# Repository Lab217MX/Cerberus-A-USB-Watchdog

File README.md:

# Cerberus

<p align="center">
  <strong>Developed by Lab217</strong><br>
  No USB gets in without permission. NONE
</p>

<p align="center">
  <sub>Proudly sponsored by</sub><br>
  
</p>

**🌐 [English](README.md) · [Español](README.es.md) · [Português](README.pt.md)**

---

## What is Cerberus?

**Cerberus is a pocket-sized device where you plug in any suspicious USB to see, in real time, what it tries to do to a computer — before you risk your own.**

Instead of blindly trusting a flash drive you found or were handed, you plug it into Cerberus first: the device pretends to be a normal PC, watches how the USB behaves, and instantly warns you if it tries to type on its own (BadUSB / Rubber Ducky), read or write files without permission, or fry the port with a voltage spike (USB Killer). Everything is shown on an OLED screen, a color LED, and over the serial port.

### Key features

- **Detects BadUSB / Rubber Ducky** — spots automated typing that's impossible for a human.
- **Detects USB Killer** — alerts on high-voltage spikes (and blocks them with the optional isolator).
- **Watches reads and writes** — warns if the USB tries to read `AUTORUN`/`README` or write/delete files on its own.
- **Suspicious-device database** — recognizes known attack hardware by its VID/PID.
- **On-device file analyzer** — recursively lists every file on the drive and identifies each one by its **magic bytes** (PNG, PDF, ELF, PE/EXE, ZIP, …), flagging files whose real type doesn't match their extension (e.g. an `.jpg` that is actually an executable). Reads file contents only, never executes.
- **Archive & polyglot inspection** — looks *inside* ZIP archives (via the central directory) for embedded executables/scripts and sweeps files for signatures hidden *after* a valid header (appended payloads / polyglots). Signature-only — nothing is decompressed, so it is immune to zip bombs.
- **Redesigned OLED GUI** — dedicated screens for the home/self-test, mass-storage detection, options menu, USB descriptors, file analyzer, hex viewer, and wipe confirmation, with on-screen `Ok`/`Bak` hints.
- **Full visibility** — OLED screen, NeoPixel LED, and serial console showing everything that happens.
- **Forensics & red team** — captures keystrokes, exports to DuckyScript, and stores info on the last device.
- **Neutralize suspicious drives** — manually wipe the MBR/GPT tables of the mounted USB (from the on-device **Wipe** menu or the `WIPE` serial command); never triggered automatically.

> Built for cybersecurity professionals (SOC, blue team, and red team) as a USB test bench, BadUSB payload debugger, and basic forensic triage tool. Built on top of [USBvalve](https://github.com/cecio/USBvalve).

---

## Installation

### Prerequisites

- Install the Arduino IDE
- `Adafruit TinyUSB Library` version `>=3.6.0`
- `Pico-PIO-USB` version `>=0.7.2`
- Boards `Raspberry Pi RP2040 (4.5.4)` with CPU Speed at `133MHz` and Tools => USB Stack set to `Adafruit TinyUSB`
- `Adafruit_SSD1306` OLED library version `>=2.5.14`
- Raspberry Pi Pico 1 or 2 (or another RP2040-based dev board)
- 128x64 or 128x32 I2C OLED display (SSD1306)

### Steps

---

#### Using the precompiled version

In GitHub, go to Releases and find the most recent `.uf2` file, then download it.

To flash the image:

- Connect the Raspberry Pi Pico with a USB cable while holding the _BOOTSEL/BOOT_ button.
- Release the button.
- A new device named `RPI-RP2` will appear on your system (on Linux you'll probably have to mount it manually).
- Copy the `.uf2` file into the folder, depending on your OLED display.
- Wait a few seconds until the device disappears.

#### Compile your own version

Get the repo locally:

```bash
git clone https://github.com/Glitchboi-sudo/Cerberus-A-USB-Watchdog.git
```

With the Arduino IDE:

- Open `Software/Cerberus/Cerberus.ino`.
- Connect the Raspberry Pi Pico with a USB cable.
- Select the Pico in Arduino.
- Tools -> USB Stack -> Adafruit TinyUSB
- Click `Upload`.

---

## Usage

The idea is simple: **Cerberus sits between your computer and the USB you want to inspect**, acting as a decoy so the suspicious device reveals its real behavior.

### Step by step

1. **Power Cerberus.** Connect it to your computer with a USB cable (the RP2040's native port). On boot, the OLED shows the home screen with "Self-Test:ok" and the LED turns **blue**: ready to go.
2. **Plug the suspicious USB** into Cerberus's host port (not into your computer).
3. **Watch the reaction in real time.** Cerberus pretends to be a PC and lets the device act. The screen, the LED, and the serial console tell you immediately what it's trying to do.
4. **Read the verdict** using the indicator table below: blue = normal, red/orange/magenta = suspicious.
5. **Inspect a storage device.** When a mass-storage drive is attached, the OLED shows a **Mass storage** detection screen; press **Ok** to open the options menu — **Info** (USB descriptors), **Files** (the magic-byte file analyzer), and **Wipe** (neutralize partition tables). In the file analyzer, pick any file to see its detected type, size, and a hex view, plus a warning if it hides an executable/appended payload.
6. **(Optional) Dig deeper over serial** for forensic analysis, keystroke capture, and the `SCAN` / `INSPECT` commands (see below).

### Screen and LED indicators

| Event                       | OLED message       | LED color |
| --------------------------- | ------------------ | --------- |
| Ready/Normal (home)         | "Self-Test:ok"     | Blue      |
| README read                 | "README (R)"       | Blue      |
| AUTORUN read                | "AUTORUN (R)"      | Blue      |
| Write detected              | "WRITING"          | Blue      |
| Delete detected             | "DELETING"         | Blue      |
| HID device connected        | "HID Device"       | Red       |
| HID sending data            | "HID Sending data" | Red       |
| Suspicious device           | "SUSP: [name]"     | Orange    |
| Automated typing (BadUSB)   | "AUTO [X] k/s"     | Magenta   |
| USB Killer detected         | "USB Killer"       | Red       |
| Mass storage detected       | "Mass storage"     | Green     |
| Wipe in progress            | "WIPING DISK"      | —         |
| Wipe complete               | "WIPE DONE"        | —         |
| Wipe error                  | "WIPE ERROR"       | —         |

### Physical buttons

The OLED is driven by four soft-keys. Every screen shows `Ok` / `Bak` hints in the bottom-right; `Up` / `Down` move the selection where a list is shown.

- **Ok** (Accept): open the options menu when a device is attached (on the home screen), enter the highlighted item, toggle hex/ASCII in the hex viewer, and confirm a wipe. On the "No device" screen, any key returns home.
- **Up / Down**: move through menu items and file lists.
- **Bak**: go back one level / exit a menu (disabled on the mass-storage detection screen, which only opens the menu).
- **BOOTSEL**:
  - Short press: reboot the device
  - Press >2 s: show the HID event count

USB descriptor pages and the partition wipe now live inside the on-device **Info** and **Wipe** menu items (no more button-hold shortcuts).

### Serial port commands

Connect over serial (SerialTinyUSB) and type these commands:

| Command    | Description                                |
| ---------- | ------------------------------------------ |
| `HELP`     | Show the list of commands                  |
| `STATUS`   | Current device status                      |
| `LAST`     | Forensic info on the last connected device |
| `RESET`    | Reset counters                             |
| `REBOOT`   | Reboot the device                          |
| `VERBOSE`  | Toggle verbose mode                        |
| `HEXDUMP`  | Toggle hex dump                            |
| `HIDDEBUG` | Toggle HID debug (raw bytes)               |
| `CLEAR`    | Clear info on the last device              |
| `WIPE`     | Neutralize the MBR/GPT tables of the mounted USB |
| `LS [path]`  | List a directory on the USB (`LS /` = volume list; `LS /N` = volume N) |
| `CAT path`   | Preview a file on the USB (text + hex)     |
| `SCAN`       | Recursively list every file with its magic-byte type, size, first bytes, and archive/polyglot warnings |
| `INSPECT path` | Deep look inside one file: ZIP entry listing + 1 MB embedded-signature sweep |
| `BROWSE`     | Open the file analyzer on the OLED         |

> On connecting a terminal, Cerberus prints a banner — wait ~2 s for it. `VERBOSE` is **off by default** (it logs every emulated-disk sector read/write and otherwise floods the console); enable it only to debug disk I/O.

---

## How does it detect threats?

Cerberus doesn't just cut the data lines: **it impersonates a real computer** so the suspicious device reveals its intentions, and it watches four fronts at once.

- **Automated typing (BadUSB / Rubber Ducky).** Cerberus measures the keystroke rate of the emulated keyboard. No human types dozens of keys per second, so when it crosses that threshold it flags an automated attack and shows the detected speed.

- **Malicious reads and writes.** Cerberus exposes a small virtual disk with bait files (`README`, `AUTORUN`). If a USB — or the malware on it — tries to read those files automatically, or write/delete content without your input, it's exposed instantly.

- **Known attack devices.** On connection, Cerberus reads the device identifiers (VID/PID) and compares them against a database of known attack hardware, warning you if it recognizes one.

- **USB Killer.** A hardware circuit monitors the port voltage; on a high-voltage spike it fires an immediate alert. With the galvanic isolator, the discharge is also **physically blocked** so it never reaches your computer.

- **Disguised files on the drive.** Beyond live behavior, Cerberus can read a mounted drive (read-only) and inspect its files without trusting it on a real PC. It identifies each file by its **magic bytes** rather than its extension — so an `invoice.pdf` that is really a Linux/Windows executable is flagged immediately — and it inspects ZIP archives (by their central directory) and sweeps for signatures appended after a valid header, catching executables smuggled inside archives or polyglot files. It is a signature pass only (nothing is run or decompressed), so it is safe even against zip bombs.

Each detection is turned right away into a message on the OLED, an LED color, and a line over the serial port, giving you a clear verdict without having to risk a real machine.

> **On magic-byte inspection:** it reads the *first* bytes of each file and the ZIP index, so it reliably flags extension/type mismatches and named executables inside archives. It does not decompress DEFLATE entries (RAM-constrained MCU), so a payload *compressed* inside an archive is identified by its entry name, not its inner magic bytes.

---

## Hardware

The `Hardware/` folder contains the project's PCB designs.

### Schematic

📄 [Cerberus schematic (PDF)](SCH_Schematic1_2026-06-15.pdf)

### CerberusZero.epro

The complete Cerberus PCB. Includes the integrated circuit with the RP2040, USB connectors, OLED display, and all necessary components.

- **Format**: EasyEDA Pro project
- **How to open**: Import into EasyEDA Pro from `File → Open`

### ADUM3160 USB Isolator

A USB galvanic isolation module based on the ADUM3160 chip. Provides **protection against USB-Killer attacks** by electrically isolating the host from the device, blocking high-voltage spikes.

- **Use**: Optional add-on for an extra layer of physical security
- **Speed**: USB 2.0 Full Speed (12 Mbps)
- **More info**: See `Hardware/ADUM3160 USB Isolator/README.md`

---

## Software Architecture

### Firmware (Cerberus.ino)

The firmware uses both cores of the RP2040:

- **Core 0**: Handles the user interface (OLED, NeoPixel LED, buttons) and emulates a USB storage device to detect suspicious host activity.
- **Core 1**: Runs the USB Host stack via PIO to monitor connected devices (HID, Mass Storage, CDC).

**Main modules:**

- **Threat detection**: USB Killer (via hardware interrupt), suspicious devices (VID/PID database), and automated BadUSB writing (HID speed analysis).
- **MSC emulation**: Virtual RAM disk that detects README/AUTORUN reads and malicious writes.
- **HID processing**: Decoding of keyboard/mouse reports with support for modifiers and special keys.
- **File analyzer**: Read-only, multi-filesystem (FAT/exFAT/NTFS/ext/ISO9660) reader that recursively lists files, types them by magic bytes, and inspects ZIP archives and appended-payload signatures. Exposed on the OLED (**Files** menu) and over serial (`SCAN` / `INSPECT`).
- **OLED interface**: Screen library (`GUI_Base.h`) with dedicated screens — home/self-test, mass-storage detection, options menu, descriptor pages, file list, hex viewer, wipe confirmation, HID/USB-Killer alerts — rendered only from core 0 to avoid cross-core I2C contention.
- **Serial commands**: Text interface for debugging and forensics (HELP, STATUS, LAST, SCAN, INSPECT, WIPE, …).

### Companion App (cerberus_listener.py) — discontinued

> ⚠️ **The desktop companion app is no longer supported and has been removed from the repository.** All monitoring and analysis now happen on-device (OLED) and over the plain serial console (`HELP`, `STATUS`, `LAST`, `SCAN`, `INSPECT`, …), which work with any serial terminal and need no extra software. Earlier versions of the app can still be found in the project's git history, but they are unmaintained and may not reflect the current firmware.

---

## Contributing

This project isn't just a repository: it's an open space to learn, experiment, and build together. **We actively welcome contributions**, whether on the technical side or even the documentation.

- **On hardware:** If you spot opportunities to improve efficiency (for example, using other chips, optimizing power consumption, or swapping components for more reliable alternatives), your suggestions are welcome!
- **On software:** From bug fixes and performance optimization to improvements in code readability or documentation; every contribution, big or small, adds up.
  You don't need to be an expert to help: if you think something can be explained better, that the code can be clearer, or that there's a more elegant way to do something, **tell us or open a Pull Request**.

---

## Credits

- Project based on [USBvalve](https://github.com/cecio/USBvalve) made by _[Cecio](https://github.com/cecio)_
- Galvanic protection based on [USB Isolator](https://github.com/wagiminator/ADuM3160-USB-Isolator) made by _[wagiminator](https://github.com/wagiminator)_
- Partition neutralizer (MBR/GPT table wiping) ported from [USB-Neutralizer](https://github.com/novamostra/USB-Neutralizer) made by _[novamostra](https://github.com/novamostra)_
- Modified / Created by:
  - [Erik Alcantara](https://www.linkedin.com/in/erik-alc%C3%A1ntara-covarrubias-29a97628a/)

---

## Sponsor

<p align="center">
  
</p>

<p align="center">
  <strong>This project was made possible thanks to the support of <a href="https://www.pcbway.com/">PCBWay</a></strong>
</p>

We thank **PCBWay** for sponsoring this project. Their high-quality PCB manufacturing service let us take Cerberus from prototype to reality. If you're looking to manufacture your own PCBs with excellent quality, competitive prices, and fast shipping, we recommend visiting [PCBWay](https://www.pcbway.com/).

---

## Open Source Hardware

<p align="center">
  
</p>

Cerberus is **certified open source hardware** by the [Open Source Hardware Association (OSHWA)](https://www.oshwa.org/).

- **Certification UID:** [MX000041](https://certification.oshwa.org/mx000041.html)
- **Country:** Mexico 🇲🇽
- **Hardware · Software · Documentation:** MIT

---

## License

This project is licensed under the **MIT License** — see the [LICENSE](LICENSE) file for details.

Hardware, software, and documentation are all released under MIT, matching the licenses declared in the project's [OSHWA certification (MX000041)](https://certification.oshwa.org/mx000041.html).

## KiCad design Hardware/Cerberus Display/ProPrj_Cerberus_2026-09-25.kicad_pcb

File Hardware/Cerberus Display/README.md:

# Cerberus Display

PCB de la placa de display (OLED + botones) del proyecto Cerberus USB Watchdog.
Proyecto editable en **KiCad**.

## Archivos

### ProPrj_Cerberus_2026-09-25.kicad_pro

Archivo de proyecto de KiCad.

- **Formato:** KiCad (`.kicad_pro`)
- **Cómo abrir:** En KiCad, `Archivo → Abrir proyecto…` y seleccionar este archivo. Abre el esquemático (`.kicad_sch`) y el PCB (`.kicad_pcb`) asociados.

### ProPrj_Cerberus_2026-09-25.kicad_sch

Esquemático de la placa (conexiones del display SSD1306, botones y cabecera hacia la placa principal).

### ProPrj_Cerberus_2026-09-25.kicad_pcb

Diseño físico del PCB (placement y ruteo).

### Bibliotecas del proyecto

- `ProPrj_Cer-easyedapro.kicad_sym` — biblioteca de símbolos.
- `ProPrj_Cerberus_2026-09-25-import-fps.pretty/` — biblioteca de footprints.
- `fp-lib-table` / `sym-lib-table` — tablas de bibliotecas de KiCad.

## Estado de fabricación

> ⏳ **Los archivos de fabricación (Gerbers y Pick & Place) aún no se liberan: la placa está en validación.** Se publicarán una vez verificada en hardware. Por ahora solo se comparte el proyecto editable de KiCad para referencia y revisión.

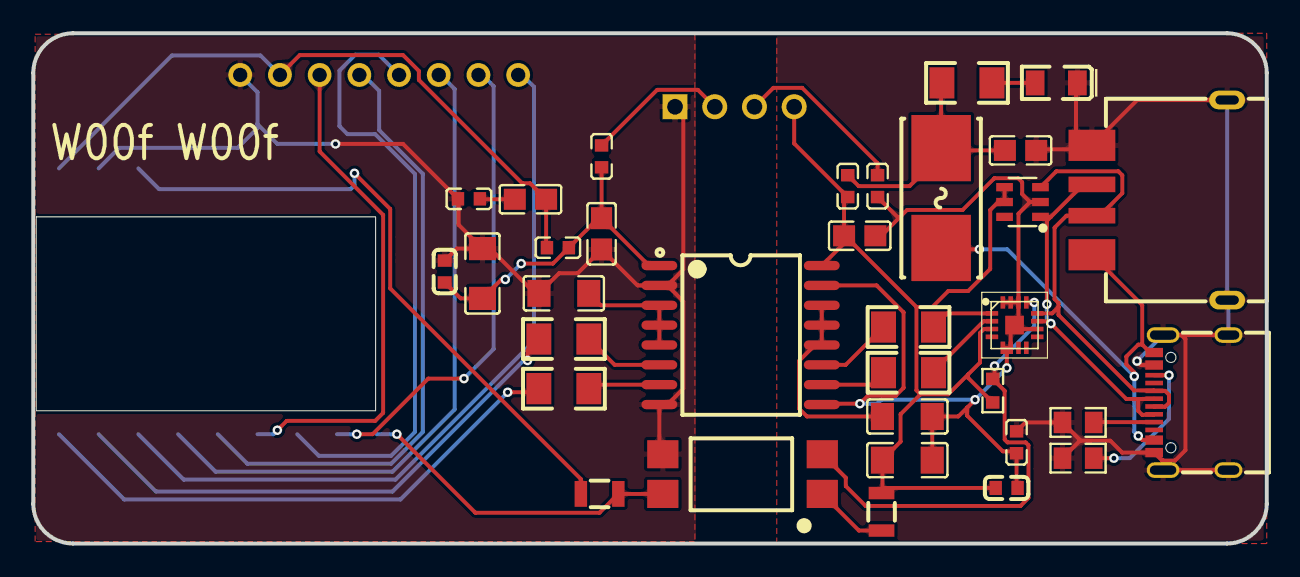
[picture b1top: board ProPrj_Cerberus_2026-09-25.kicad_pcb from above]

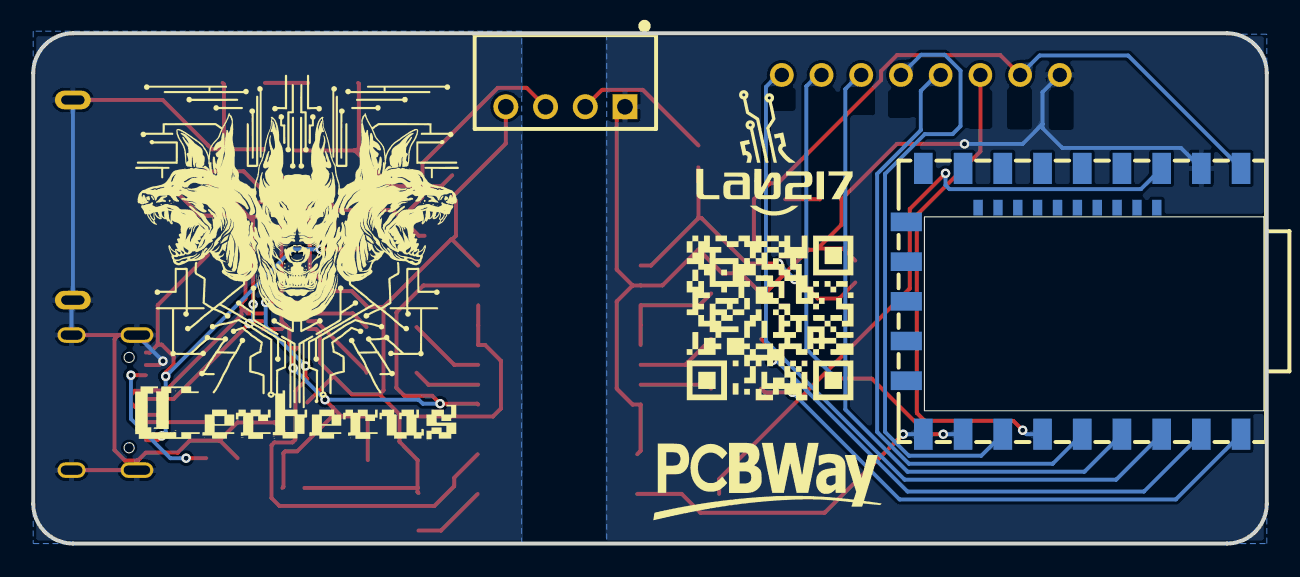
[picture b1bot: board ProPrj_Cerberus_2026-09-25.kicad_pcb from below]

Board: 2 copper layers, 78.9 x 32.6 mm, 37 parts (2 on the bottom side), 36 nets.

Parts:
C2, C14, C33, C34: C0805
C3, C4, C5, C32: C1206
C7, C8: C0603
D2: SOT-23-6_L2.9-W1.6-P0.95-LS2.8-BL
D3: D1206-RD_S13773
F2: FUSE-SMD_L9.7-W5.0
FB1, FB2, FB3, FB4: L0603
L1, L2: L0603
R1, R2, R4, R8, R18: R1206_1
R3, R5: R0805
R20, R21: RES-SMD_L3.2-W1.6_HCS1206FTL500
R22: R0603
U1: SOIC-16_L10.3-W7.5-P1.27-LS10.3-TL
U2: SOP-4_L6.5-W4.6-P2.54-LS10.2-TL
U4: SSD1306 128X64 4KEYS
U11: PWRM-TH_BXXXXS-1W
U15: COMM-SMD_RP2040-ZERO
U16: QFN50P300X300X100-17N
USB1: TYPE-C-SMD_LAIL-TYPE-C-16PIN-08-WT
USB2: USB-A-SMD_USB-100SD-F2

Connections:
3V3: R21.2, U15.21
$2N7232: D3.2, R8.2
$2N8019: R1.2, U1.6
$2N8020: R2.2, U1.7
$2N8021: R4.1, U1.10
$2N8022: R18.1, U1.11
$2N8501: L1.2, U11.2
$2N8502: L2.2, U11.3
$2N13465: R20.1, U2.1
$2N22688: R18.2, U16.1
$2N22689: R4.2, U16.2
$2N22702: R3.2, USB1.A5
$2N22703: R5.2, USB1.B5
$2N22723: C14.1, FB2.2
CON_DN: D2.1, U16.11, USB1.A7, USB1.B7, USB2.3
CON_DP: D2.3, U16.12, USB1.A6, USB1.B6, USB2.2
FLAG_KILL: R22.1, U2.2, U16.13
GND: C3.1, C4.1, C7.1, C33.2, FB2.1, U1.2, U1.8, U2.3, U4.1, U11.1, U15.22
GND2: C5.1, C8.1, C32.1, C34.2, D2.2, FB4.1, L2.1, U1.9, U1.15, U16.5, U16.6, U16.10, U16.14, U16.15, U16.16, U16.17
GOUT: C2.1, D3.1, FB4.2, R3.1, R5.1, USB1.13, USB1.14, USB1.15, USB1.16, USB1.A1B12, USB1.B4A9, USB2.4, USB2.5, USB2.6
GPIO0: R2.1, U15.1
GPIO1: R1.1, U15.2
GPIO2: U4.8, U15.3
GPIO3: U4.6, U15.4
GPIO4: U4.4, U15.5
GPIO5: U4.3, U15.6
GPIO6: U4.5, U15.7
GPIO7: U4.7, U15.8
GPIO8: R21.1, U2.4, U15.9
VBUS1: C3.2, C7.2, C33.1, FB1.2, L1.1, U1.1
VBUS2: C8.2, C32.2, C34.1, D2.4, D2.5, FB3.1, R20.2, R22.2, U1.16, U11.4, U16.3
VDD1: C4.2, U1.3, U1.4, U1.5
VDD2: C5.2, U1.12, U1.13, U1.14
VOUT: C2.2, F2.1, FB3.2, R8.1
VSYS: C14.2, FB1.1, U4.2, U15.23
V_FUSE: F2.2, USB1.A4B9, USB1.B1A12, USB2.1

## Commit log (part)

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2026-04-16 Upload: Gerger incluido
2026-04-17 FIx: Añadir Sponsor
2026-06-04 Update README.md
    Cambio de propietario
2026-06-16 Update README - Various Languages

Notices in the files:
README.md:
License: MIT
